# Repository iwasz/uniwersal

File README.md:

# uniwersal
Universal board and shields for it. Below is a photo of version 1.0

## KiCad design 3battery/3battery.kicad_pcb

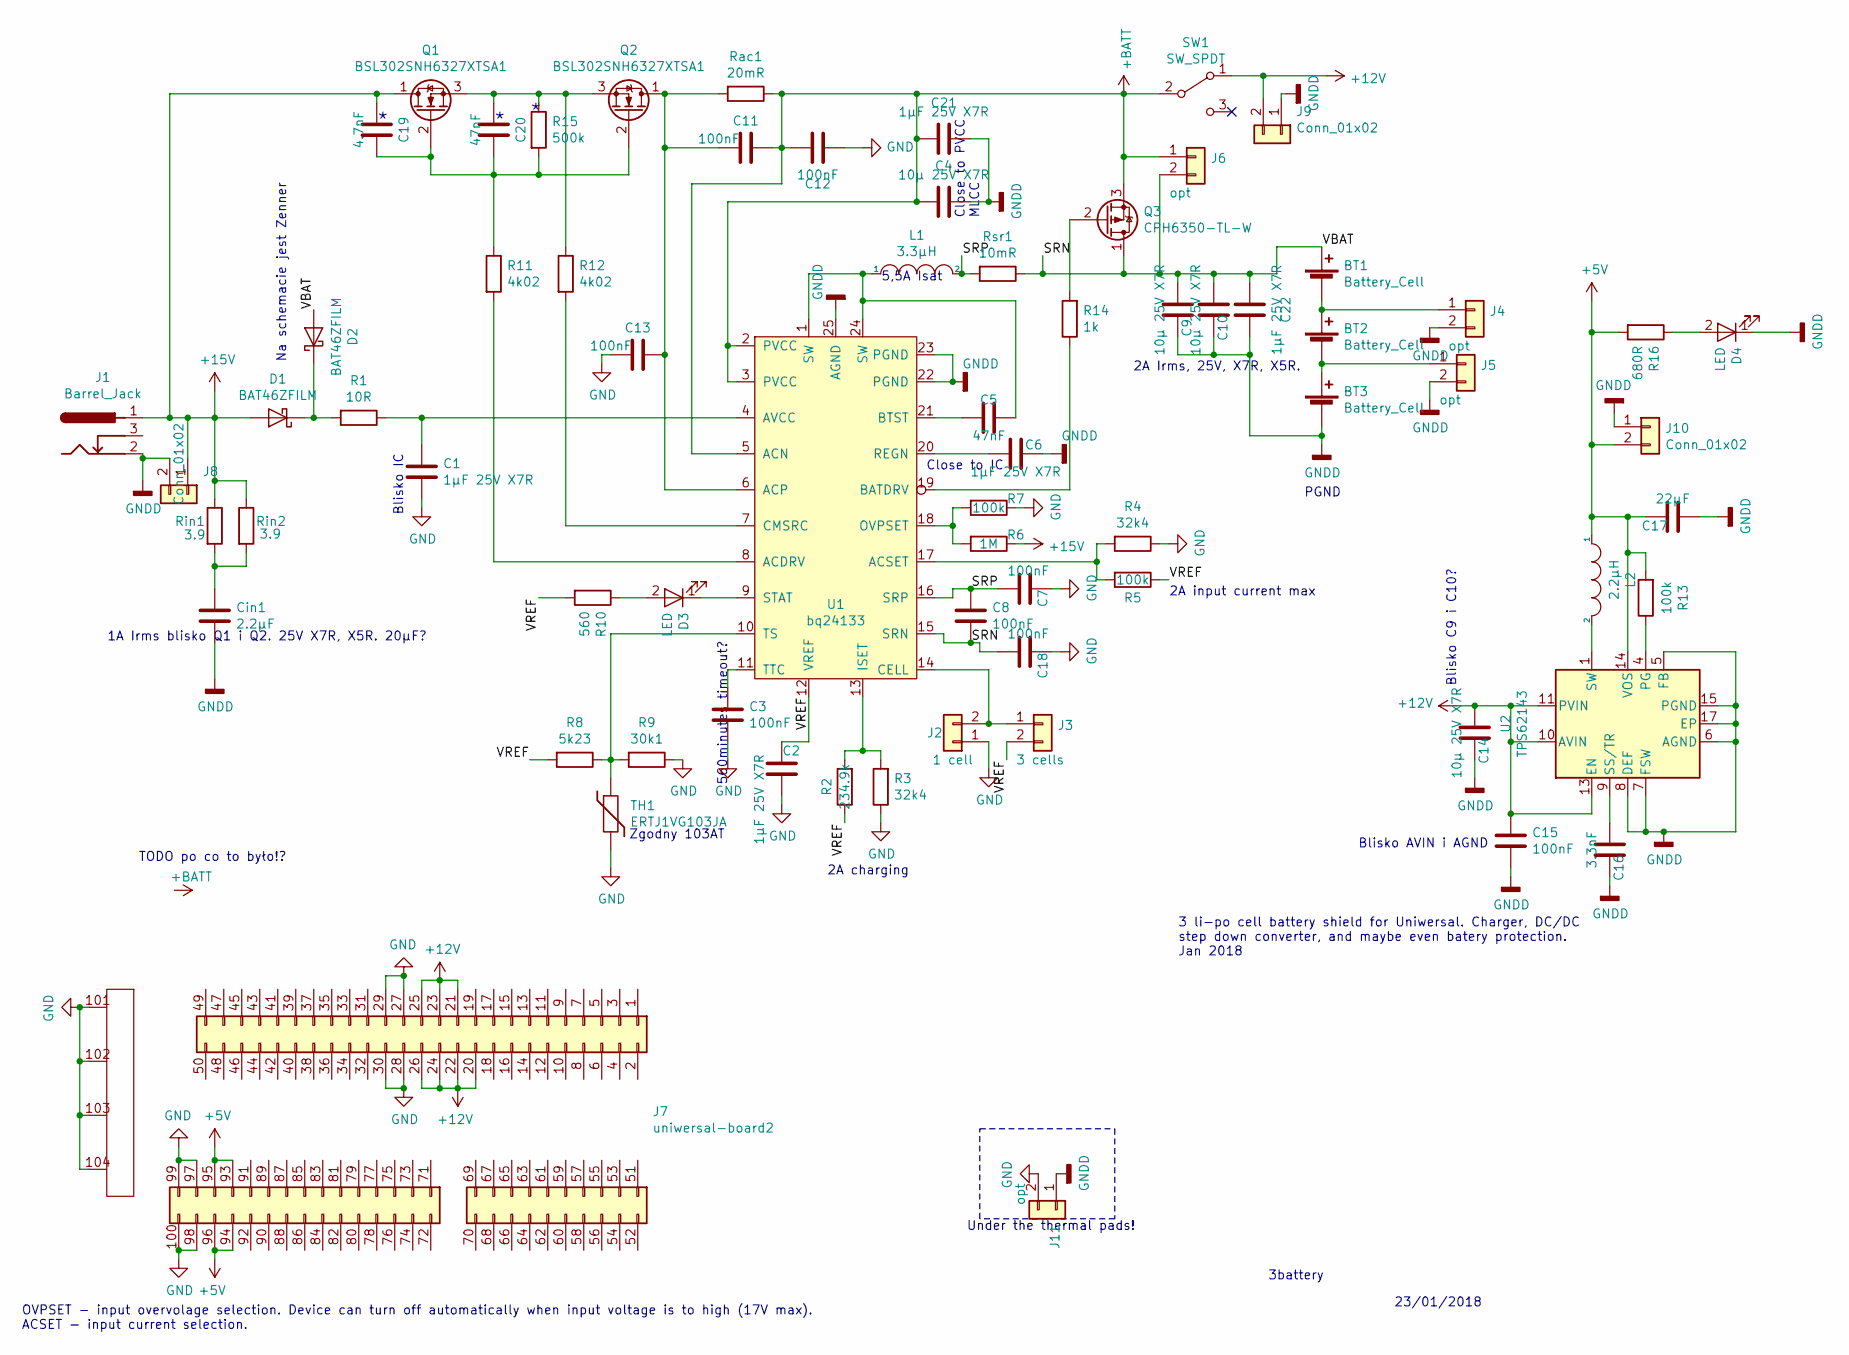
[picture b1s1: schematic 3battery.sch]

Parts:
BT1, BT2, BT3: Battery_Cell; BLM-BH18650-PC2
C1, C2, C6, C21, C22: 1µF 25V X7R; C_0805_2012Metric
C3, C7, C8, C11, C12, C13, C15, C18: 100nF; C_0603_1608Metric
C4, C9, C10, C14: 10µ 25V X7R; C_1206_3216Metric
C5, C20: 47nF; C_0603_1608Metric
C16: 3.3nF; C_0603_1608Metric
C17: 22µF; C_1206_3216Metric
C19: 4.7nF; C_0603_1608Metric
Cin1: 2.2µF; C_0805_2012Metric
D1, D2: BAT46ZFILM; D_SOD-123
D3, D4: LED; D_0805_2012Metric
J1: Barrel_Jack; BarrelJack_Horizontal
J2: 1 cell; SolderJumper-2_P1.3mm_Open_RoundedPad1.0x1.5mm
J3: 3 cells; SolderJumper-2_P1.3mm_Bridged_RoundedPad1.0x1.5mm
J4, J5, J6: opt; SolderJumper-2_P1.3mm_Open_RoundedPad1.0x1.5mm
J7: uniwersal-board2; uniwersal-board
J8, J9, J10: Conn_01x02; PinHeader_1x02_P2.54mm_Vertical
J11: opt; R_0402_1005Metric
L1: 3.3µH; L_7.3x7.3_H3.5
L2: 2.2µH; L_6.3x6.3_H3
Q1, Q2: BSL302SNH6327XTSA1; TSOP-6_1.65x3.05mm_P0.95mm-BSLMOSFET
Q3: CPH6350-TL-W; TSOT-23-6-POWER_MOSFET
R1: 10R; R_1206_3216Metric
R2: 234.9k; R_0603_1608Metric
R3, R4: 32k4; R_0603_1608Metric
R5, R7, R13: 100k; R_0603_1608Metric
R6: 1M; R_0603_1608Metric
R8: 5k23; R_0603_1608Metric
R9: 30k1; R_0603_1608Metric
R10: 560; R_0603_1608Metric
R11, R12: 4k02; R_0603_1608Metric
R14: 1k; R_0603_1608Metric
R15: 500k; R_0603_1608Metric
R16: 680R; R_0603_1608Metric
Rac1: 20mR; R_1206_3216Metric
Rin1, Rin2: 3.9; R_2010_5025Metric
Rsr1: 10mR; R_1206_3216Metric
SW1: SW_SPDT; SW_CuK_OS102011MA1QN1_SPDT_Angled
TH1: ERTJ1VG103JA; R_0603_1608Metric
U1: bq24133; R-PVQFN-N24
U2: TPS62143; QFN-16-1EP_3x3mm_P0.5mm_EP2.7x2.7mm_ThermalVias

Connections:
+5V: C17.1, J7.93 (Pin_23), J7.94 (Pin_24), J7.95 (Pin_25), J7.96 (Pin_26), J10.2, L2.1, R13.2, R16.2, U2.14 (VOS)
+12V: C14.2, C15.1, J7.20, J7.21, J7.22, J7.23, J7.24, J7.25, J7.26, J9.2, SW1.1 (A), U2.10 (AVIN), U2.11 (PVIN), U2.12 (PVIN), U2.13 (EN)
+15V: C19.1, D1.2 (A), J1.1, J8.1, Q1.1 (D), R6.1, Rin1.1, Rin2.1
+BATT: C4.2, C11.2, C12.1, C21.2, J6.1, Q3.3 (S), Rac1.1, SW1.2 (B), U1.2 (PVCC), U1.3 (PVCC), U1.5 (ACN)
/SRN: BT1.1 (+), C8.2, C9.2, C10.2, C18.2, C22.2, D2.2 (A), J6.2, Q3.1 (D), Rsr1.1, U1.15 (SRN)
/SRP: C7.2, C8.1, L1.2, Rsr1.2, U1.16 (SRP)
/VREF: C2.1, J3.2, R2.1, R5.1, R8.2, R10.2, U1.12 (VREF)
GND: C1.2, C2.2, C3.2, C7.1, C12.2, C13.1, C18.1, J2.1, J7.27, J7.28, J7.29, J7.30, J7.97 (Pin_27), J7.98 (Pin_28), J7.99 (Pin_29), J7.100 (Pin_30), J7.101, J7.102, J7.103, J7.104, J11.2, R3.1, R4.1, R7.1, R9.1, TH1.2
GNDD: BT3.2 (-), C4.1, C6.1, C9.1, C10.1, C14.1, C15.2, C16.1, C17.2, C21.1, C22.1, Cin1.2, D4.1 (K), J1.2, J4.2, J5.2, J8.2, J9.1, J10.1, J11.1, U1.22 (PGND), U1.23 (PGND), U1.25 (AGND), U2.5 (FB), U2.6 (AGND), U2.7 (FSW), U2.8 (DEF), U2.15 (PGND), U2.16 (PGND), U2.17 (EP)
unnamed: BT1.2 (-), BT2.1 (+), J4.1
unnamed: BT2.2 (-), BT3.1 (+), J5.1
unnamed: C1.1, R1.1, U1.4 (AVCC)
unnamed: C3.1, U1.11 (TTC)
unnamed: C5.1, L1.1, U1.1 (SW), U1.24 (SW)
unnamed: C5.2, U1.21 (BTST)
unnamed: C6.2, U1.20 (REGN)
unnamed: C11.1, C13.2, Q2.1 (D), Rac1.2, U1.6 (ACP)
unnamed: C16.2, U2.9 (SS/TR)
unnamed: C19.2, C20.2, Q1.2 (G), Q2.2 (G), R11.1, R15.2
unnamed: C20.1, Q1.3 (S), Q2.3 (S), R12.1, R15.1
unnamed: Cin1.1, Rin1.2, Rin2.2
unnamed: D1.1 (K), D2.1 (K), R1.2
unnamed: D3.1 (K), U1.9 (STAT)
unnamed: D3.2 (A), R10.1
unnamed: D4.2 (A), R16.1
unnamed: J2.2, J3.1, U1.14 (CELL)
unnamed: L2.2, U2.1 (SW), U2.2 (SW), U2.3 (SW)
unnamed: Q3.2 (G), R14.2
unnamed: R2.2, R3.2, U1.13 (ISET)
unnamed: R4.2, R5.2, U1.17 (ACSET)
unnamed: R6.2, R7.2, U1.18 (OVPSET)
unnamed: R8.1, R9.2, TH1.1, U1.10 (TS)
unnamed: R11.2, U1.8 (ACDRV)
unnamed: R12.2, U1.7 (CMSRC)
unnamed: R13.1, U2.4 (PG)
unnamed: R14.1, U1.19 (BATDRV)

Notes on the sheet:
Na schemacie jest Zenner
Blisko IC
3battery
23/01/2018
3 li-po cell battery shield for Uniwersal. Charger, DC/DC step down converter, and maybe even batery protection. Jan 2018
Blisko C9 i C10?
Blisko AVIN i AGND
OVPSET - input overvolage selection. Device can turn off automatically when input voltage is to high (17V max). ACSET - input current selection.
PGND
Close to PVCC MLCC
Close to IC
2A charging
2A input current max
560minutes timeout?
Zgodny 103AT
5,5A Isat
1A Irms blisko Q1 i Q2. 25V X7R, X5R. 20µF?
2A Irms, 25V, X7R, X5R.
Under the thermal pads!
TODO po co to było!?

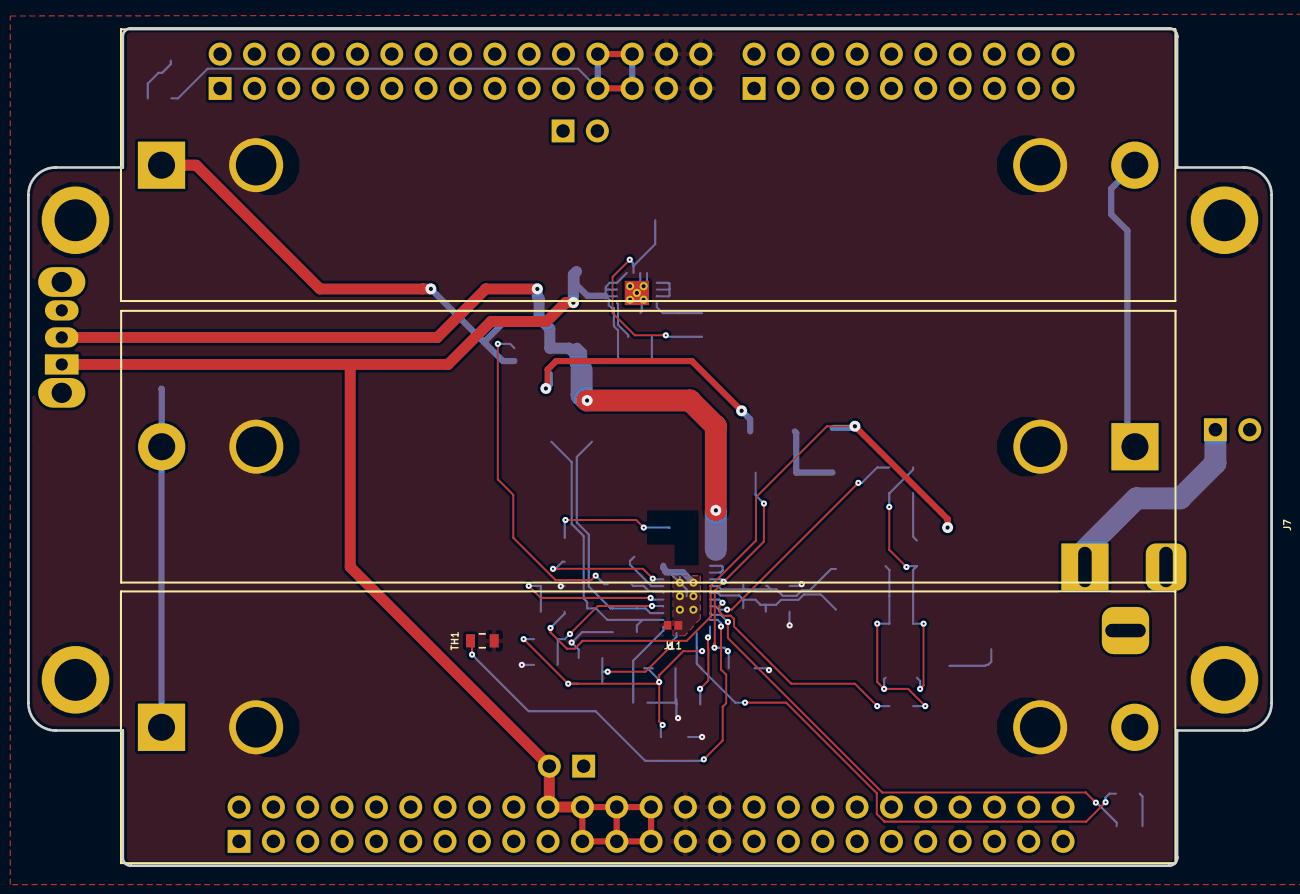
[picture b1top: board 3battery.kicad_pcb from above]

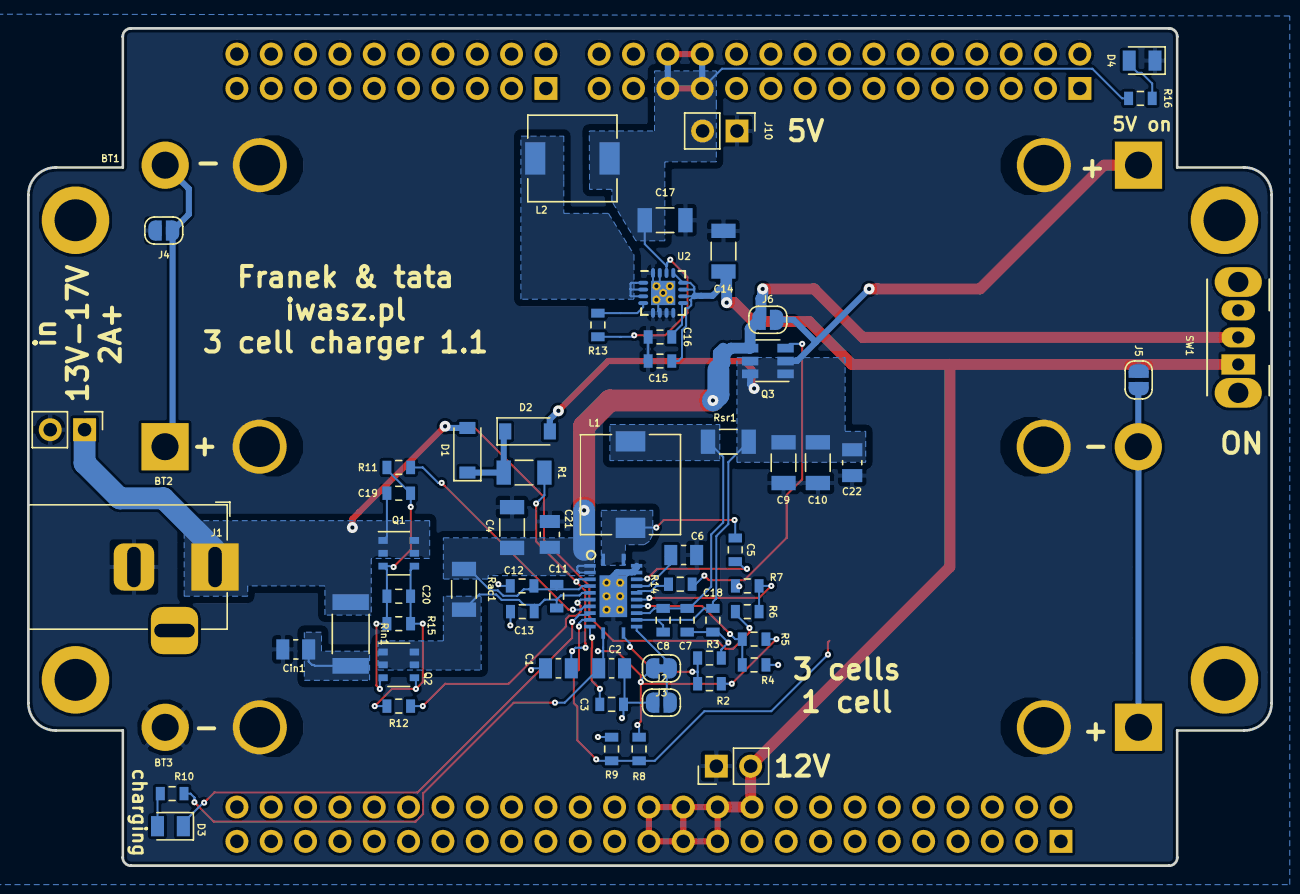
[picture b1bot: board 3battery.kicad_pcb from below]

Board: 2 copper layers, 92.0 x 61.9 mm, 69 parts (63 on the bottom side), 36 nets.

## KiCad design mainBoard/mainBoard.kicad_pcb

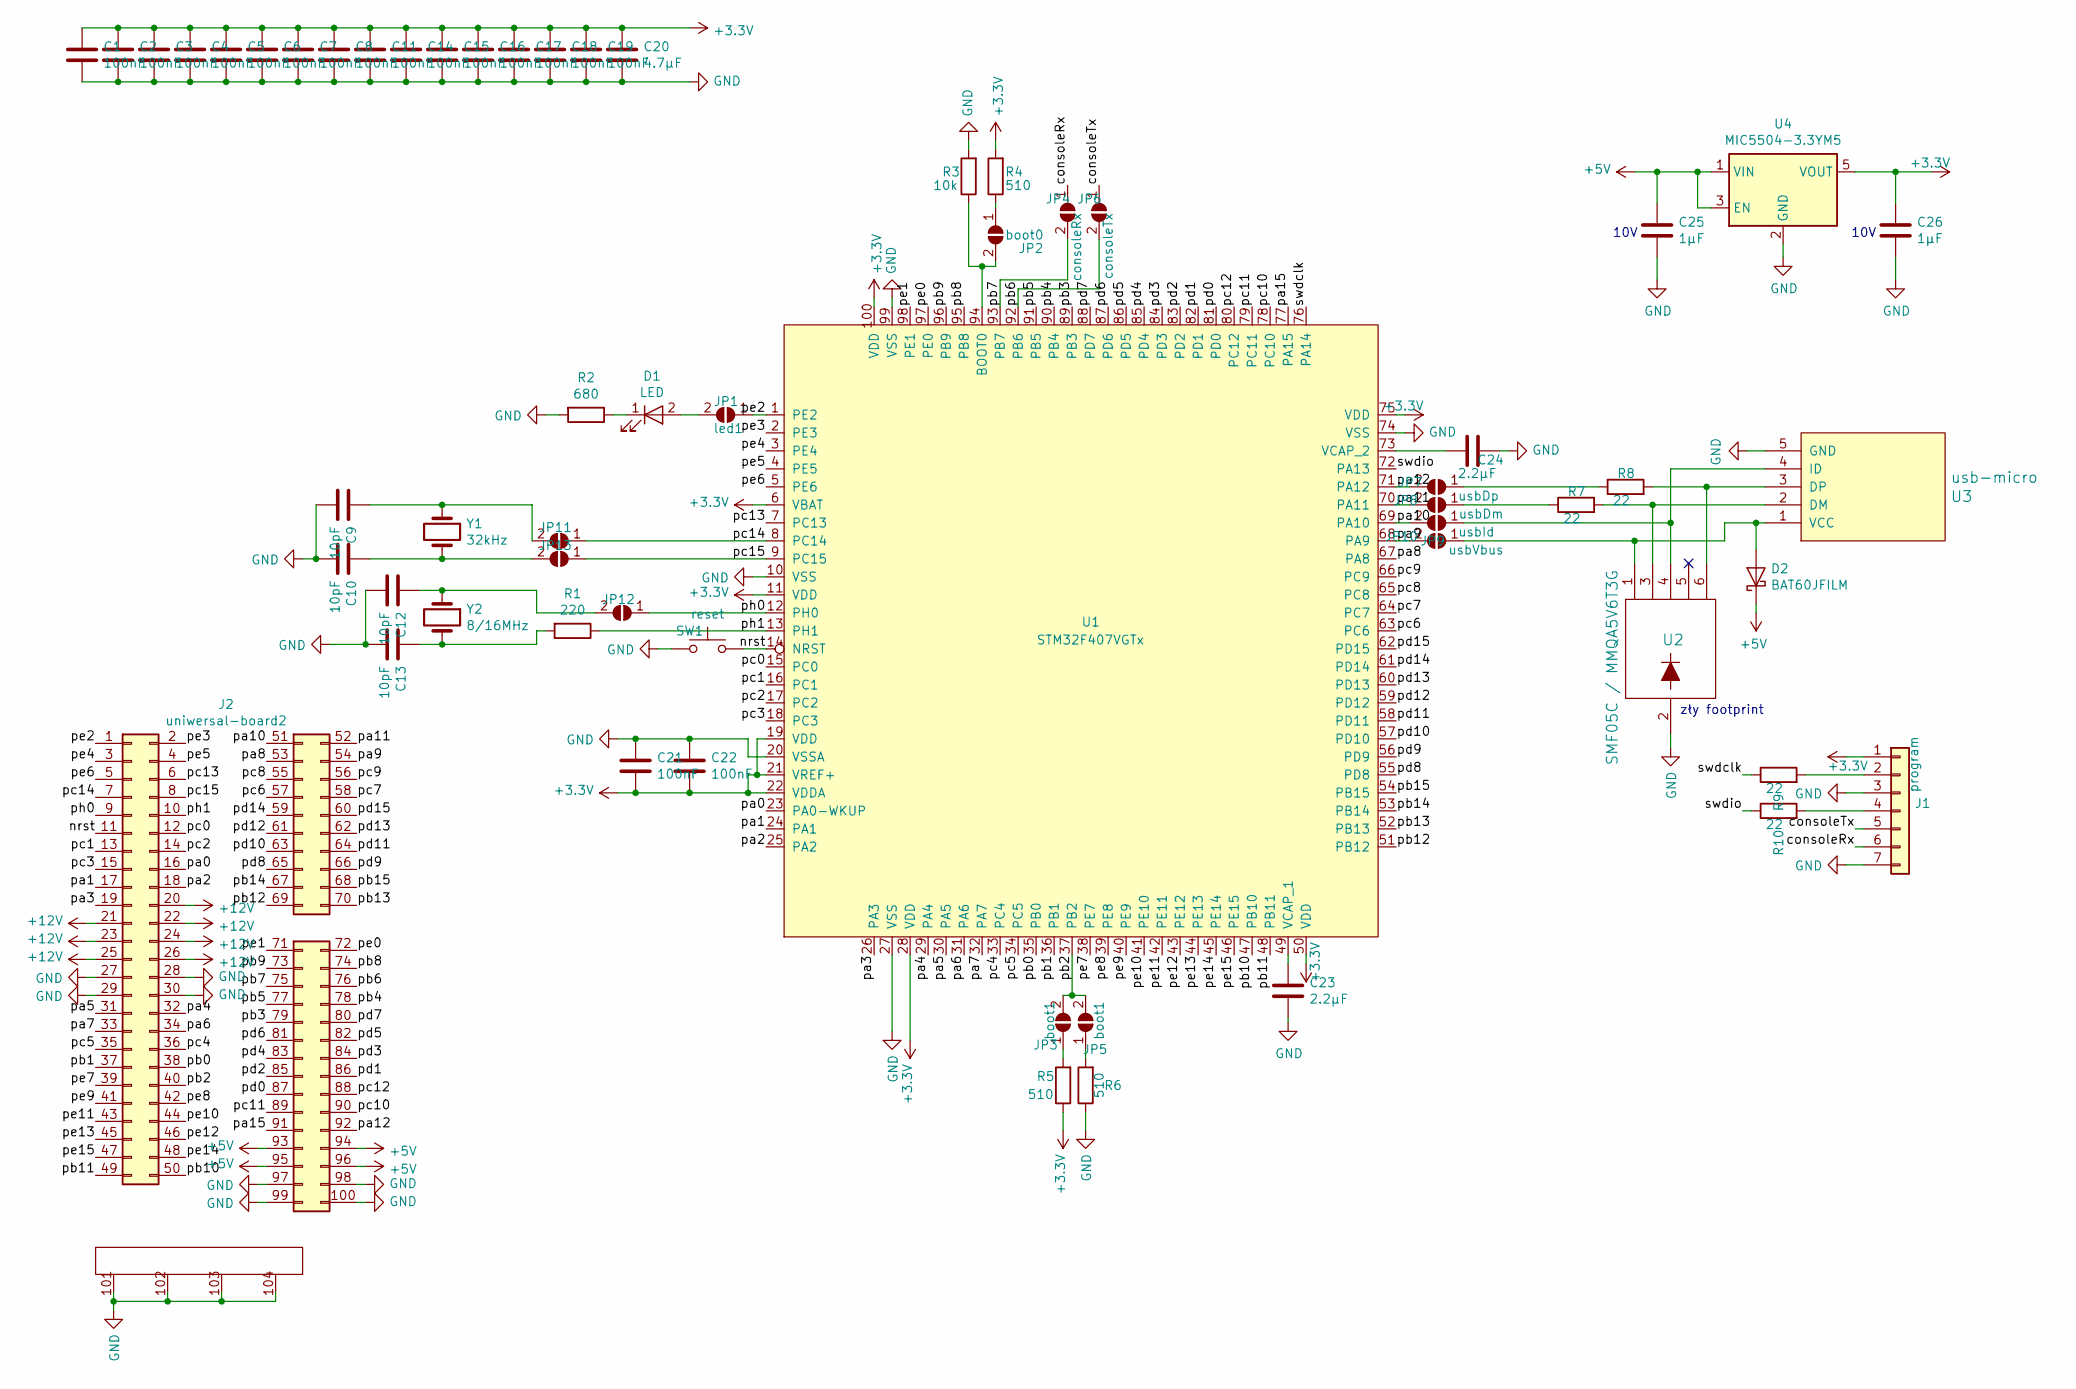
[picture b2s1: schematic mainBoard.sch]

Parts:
C1, C2, C3, C4, C5, C6, C7, C8, C11, C14, C15, C16, C17, C18, C19, C21, C22: 100nF; C_0603_1608Metric
C9, C10, C12, C13: 10pF; C_0603_1608Metric
C20: 4.7µF; C_1206_3216Metric
C23, C24: 2.2µF; C_1206_3216Metric
C25, C26: 1µF; C_0805_2012Metric
D1: LED; LED_0805_2012Metric
D2: BAT60JFILM; D_SOD-323
J1: program; PinHeader_1x07_P2.00mm_Vertical
J2: uniwersal-board2; uniwersal-board
JP1: led1; SolderJumper-2_P1.3mm_Open_RoundedPad1.0x1.5mm
JP2: boot0; SolderJumper-2_P1.3mm_Open_RoundedPad1.0x1.5mm
JP3, JP5: boot1; SolderJumper-2_P1.3mm_Open_RoundedPad1.0x1.5mm
JP4: consoleRx; SolderJumper-2_P1.3mm_Bridged_RoundedPad1.0x1.5mm
JP6: consoleTx; SolderJumper-2_P1.3mm_Bridged_RoundedPad1.0x1.5mm
JP7: usbDp; SolderJumper-2_P1.3mm_Bridged_RoundedPad1.0x1.5mm
JP8: usbDm; SolderJumper-2_P1.3mm_Bridged_RoundedPad1.0x1.5mm
JP9: usbId; SolderJumper-2_P1.3mm_Open_RoundedPad1.0x1.5mm
JP10: usbVbus; SolderJumper-2_P1.3mm_Open_RoundedPad1.0x1.5mm
JP11, JP13: x; SolderJumper-2_P1.3mm_Open_RoundedPad1.0x1.5mm
JP12: x32; SolderJumper-2_P1.3mm_Bridged_RoundedPad1.0x1.5mm
R1: 220; R_0603_1608Metric
R2: 680; R_0603_1608Metric
R3: 10k; R_0603_1608Metric
R4, R5, R6: 510; R_0603_1608Metric
R7, R8, R9, R10: 22; R_0603_1608Metric
SW1: reset; SW_Tactile_SPST_Angled_PTS645Vx83-2LFS
U1: STM32F407VGTx; LQFP-100_14x14mm_P0.5mm
U2: SMF05C / MMQA5V6T3G; SOT-363_SC-70-6
U3: usb-micro; conn_usb_B_micro_smd-2-nohole
U4: MIC5504-3.3YM5; SOT-23-5
Y1: 32kHz; Crystal_C38-LF_D3.0mm_L8.0mm_Horizontal
Y2: 8/16MHz; Crystal_HC49-4H_Vertical

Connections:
+3V3: C1.1, C2.1, C3.1, C4.1, C5.1, C6.1, C7.1, C8.1, C11.1, C14.1, C15.1, C16.1, C17.1, C18.1, C19.1, C20.1, C21.1, C22.2, C26.1, J1.1, R4.2, R5.1, U1.6 (VBAT), U1.11 (VDD), U1.19 (VDD), U1.21 (VREF+), U1.22 (VDDA), U1.28 (VDD), U1.50 (VDD), U1.75 (VDD), U1.100 (VDD), U4.5 (VOUT)
+5V: C25.1, D2.1 (K), J2.93 (Pin_23), J2.94 (Pin_24), J2.95 (Pin_25), J2.96 (Pin_26), U4.1 (VIN), U4.3 (EN)
+12V: J2.20, J2.21, J2.22, J2.23, J2.24, J2.25, J2.26
/consoleRx: J1.6, JP4.1 (A)
/consoleTx: J1.5, JP6.1 (A)
/nrst: J2.11, SW1.2, U1.14 (NRST)
/pa0: J2.16, U1.23 (PA0-WKUP)
/pa1: J2.17, U1.24 (PA1)
/pa2: J2.18, U1.25 (PA2)
/pa3: J2.19, U1.26 (PA3)
/pa4: J2.32, U1.29 (PA4)
/pa5: J2.31, U1.30 (PA5)
/pa6: J2.34, U1.31 (PA6)
/pa7: J2.33, U1.32 (PA7)
/pa8: J2.53 (Pin_3), U1.67 (PA8)
/pa9: J2.54, JP10.2 (B), U1.68 (PA9)
/pa10: J2.51 (Pin_1), JP9.2 (B), U1.69 (PA10)
/pa11: J2.52 (Pin_2), JP8.2 (B), U1.70 (PA11)
/pa12: J2.92 (Pin_22), JP7.2 (B), U1.71 (PA12)
/pa15: J2.91 (Pin_21), U1.77 (PA15)
/pb0: J2.38, U1.35 (PB0)
/pb1: J2.37, U1.36 (PB1)
/pb2: J2.40, JP3.2 (B), JP5.2 (B), U1.37 (PB2)
/pb3: J2.79 (Pin_9), U1.89 (PB3)
/pb4: J2.78 (Pin_8), U1.90 (PB4)
/pb5: J2.77 (Pin_7), U1.91 (PB5)
/pb6: J2.76 (Pin_6), JP6.2 (B), U1.92 (PB6)
/pb7: J2.75 (Pin_5), JP4.2 (B), U1.93 (PB7)
/pb8: J2.74 (Pin_4), U1.95 (PB8)
/pb9: J2.73 (Pin_3), U1.96 (PB9)
/pb10: J2.50, U1.47 (PB10)
/pb11: J2.49, U1.48 (PB11)
/pb12: J2.69, U1.51 (PB12)
/pb13: J2.70 (Pin_20), U1.52 (PB13)
/pb14: J2.67 (Pin_17), U1.53 (PB14)
/pb15: J2.68 (Pin_18), U1.54 (PB15)
/pc0: J2.12, U1.15 (PC0)
/pc1: J2.13, U1.16 (PC1)
/pc2: J2.14, U1.17 (PC2)
/pc3: J2.15, U1.18 (PC3)
/pc4: J2.36, U1.33 (PC4)
/pc5: J2.35, U1.34 (PC5)
/pc6: J2.57 (Pin_7), U1.63 (PC6)
/pc7: J2.58 (Pin_8), U1.64 (PC7)
/pc8: J2.55 (Pin_5), U1.65 (PC8)
/pc9: J2.56 (Pin_6), U1.66 (PC9)
/pc10: J2.90 (Pin_20), U1.78 (PC10)
/pc11: J2.89 (Pin_19), U1.79 (PC11)
/pc12: J2.88 (Pin_18), U1.80 (PC12)
/pc13: J2.6, U1.7 (PC13)
/pc14: J2.7, JP11.1 (A), U1.8 (PC14)
/pc15: J2.8, JP13.1 (A), U1.9 (PC15)
/pd0: J2.87 (Pin_17), U1.81 (PD0)
/pd1: J2.86 (Pin_16), U1.82 (PD1)
/pd2: J2.85 (Pin_15), U1.83 (PD2)
/pd3: J2.84 (Pin_14), U1.84 (PD3)
/pd4: J2.83 (Pin_13), U1.85 (PD4)
/pd5: J2.82 (Pin_12), U1.86 (PD5)
/pd6: J2.81, U1.87 (PD6)
/pd7: J2.80 (Pin_10), U1.88 (PD7)
/pd8: J2.65 (Pin_15), U1.55 (PD8)
/pd9: J2.66 (Pin_16), U1.56 (PD9)
/pd10: J2.63 (Pin_13), U1.57 (PD10)
/pd11: J2.64 (Pin_14), U1.58 (PD11)
/pd12: J2.61 (Pin_11), U1.59 (PD12)
/pd13: J2.62, U1.60 (PD13)
/pd14: J2.59 (Pin_9), U1.61 (PD14)
/pd15: J2.60 (Pin_10), U1.62 (PD15)
/pe0: J2.72 (Pin_2), U1.97 (PE0)
/pe1: J2.71 (Pin_1), U1.98 (PE1)
/pe2: J2.1, JP1.1 (A), U1.1 (PE2)
/pe3: J2.2, U1.2 (PE3)
/pe4: J2.3, U1.3 (PE4)
/pe5: J2.4, U1.4 (PE5)
/pe6: J2.5, U1.5 (PE6)
/pe7: J2.39, U1.38 (PE7)
/pe8: J2.42, U1.39 (PE8)
/pe9: J2.41, U1.40 (PE9)
/pe10: J2.44, U1.41 (PE10)
/pe11: J2.43, U1.42 (PE11)
/pe12: J2.46, U1.43 (PE12)
/pe13: J2.45, U1.44 (PE13)
/pe14: J2.48, U1.45 (PE14)
/pe15: J2.47, U1.46 (PE15)
/ph0: J2.9, JP12.1 (A), U1.12 (PH0)
/ph1: J2.10, R1.1, U1.13 (PH1)
/swdclk: R9.1, U1.76 (PA14)
/swdio: R10.1, U1.72 (PA13)
GND: C1.2, C2.2, C3.2, C4.2, C5.2, C6.2, C7.2, C8.2, C9.1, C10.1, C11.2, C12.1, C13.1, C14.2, C15.2, C16.2, C17.2, C18.2, C19.2, C20.2, C21.2, C22.1, C23.2, C24.1, C25.2, C26.2, J1.3, J1.7, J2.27, J2.28, J2.29, J2.30, J2.97 (Pin_27), J2.98 (Pin_28), J2.99 (Pin_29), J2.100 (Pin_30), J2.101, J2.102, J2.103, J2.104, R2.2, R3.2, R6.1, SW1.1, U1.10 (VSS), U1.20 (VSSA), U1.27 (VSS), U1.74 (VSS), U1.99 (VSS), U2.2, U3.5 (GND), U4.2 (GND)
unnamed: C9.2, JP11.2 (B), Y1.1
unnamed: C10.2, JP13.2 (B), Y1.2
unnamed: C12.2, JP12.2 (B), Y2.1
unnamed: C13.2, R1.2, Y2.2
unnamed: C23.1, U1.49 (VCAP_1)
unnamed: C24.2, U1.73 (VCAP_2)
unnamed: D1.1 (K), R2.1
unnamed: D1.2 (A), JP1.2 (B)
unnamed: D2.2 (A), JP10.1 (A), U2.1, U3.1 (VCC)
unnamed: J1.2, R9.2
unnamed: J1.4, R10.2
unnamed: JP2.1 (A), R4.1
unnamed: JP2.2 (B), R3.1, U1.94 (BOOT0)
unnamed: JP3.1 (A), R5.2
unnamed: JP5.1 (A), R6.2
unnamed: JP7.1 (A), R8.1
unnamed: JP8.1 (A), R7.1
unnamed: JP9.1 (A), U2.4, U3.4 (ID)
unnamed: R7.2, U2.3, U3.2 (DM)
unnamed: R8.2, U2.6, U3.3 (DP)

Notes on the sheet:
10V
zły footprint

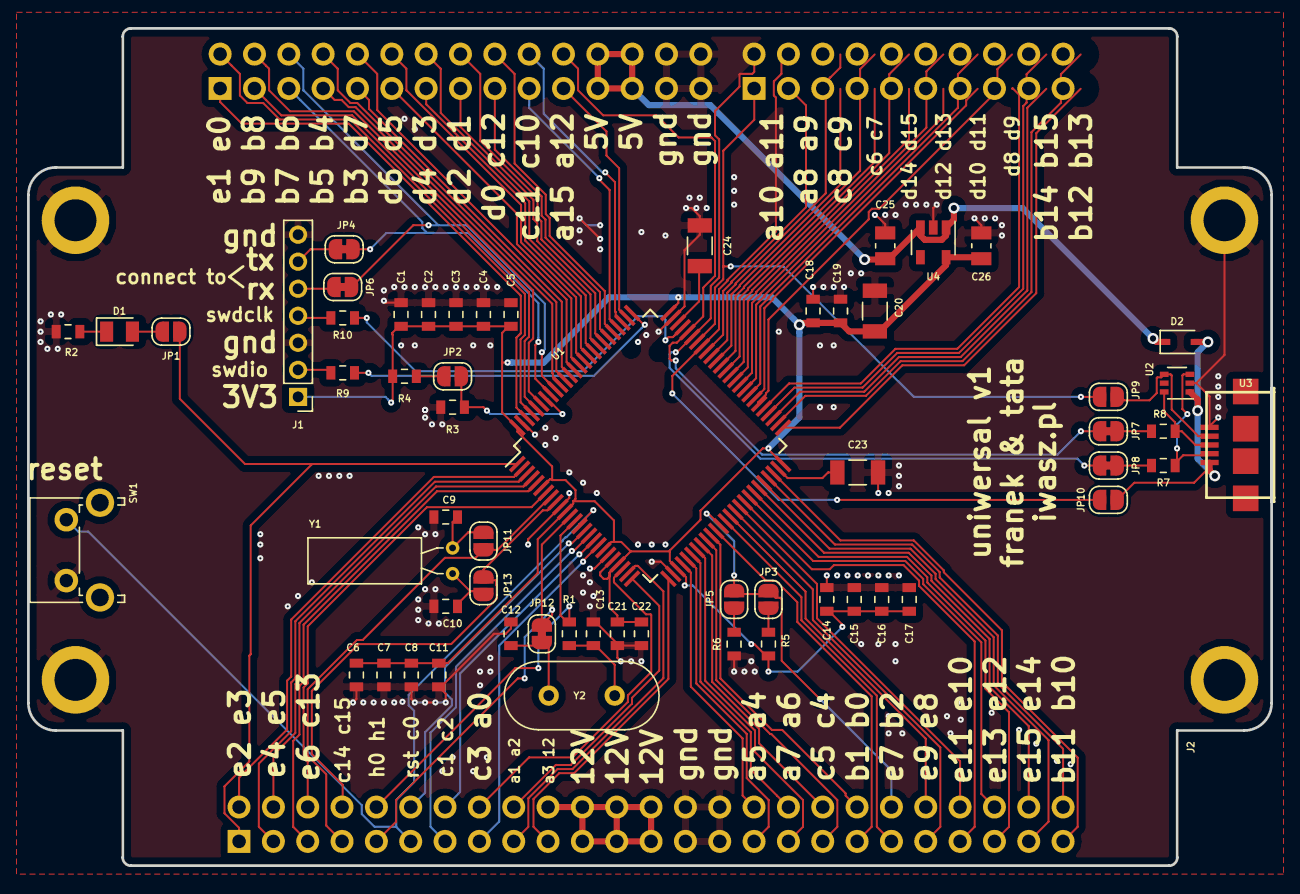
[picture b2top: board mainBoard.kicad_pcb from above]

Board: 2 copper layers, 92.0 x 61.9 mm, 60 parts (0 on the bottom side), 109 nets.

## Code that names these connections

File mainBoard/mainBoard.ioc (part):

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Mcu.Name=STM32F407V(E-G)Tx
Mcu.Package=LQFP100
Mcu.UserName=STM32F407VGTx
PA10.Mode=OTG/Dual_Role_Device
PA10.Signal=USB_OTG_FS_ID
PA11.Mode=OTG/Dual_Role_Device
PA11.Signal=USB_OTG_FS_DM
PA12.Mode=OTG/Dual_Role_Device
PA12.Signal=USB_OTG_FS_DP
PA9.Signal=GPIO_Input
PB6.Mode=Asynchronous
PB6.Signal=USART1_TX
PB7.Mode=Asynchronous
PB7.Signal=USART1_RX
PE2.Signal=GPIO_Output
RCC.HSE_VALUE=25000000
RCC.SYSCLKFreq_VALUE=16000000

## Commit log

2018-01-30 Initial
2018-02-04 Main board and proto-board added
2018-02-05 4 layers, but I plan to make it only 2.
2018-02-07 Gerbers directory added, and domcumentation improved
2018-04-09 Bug-fixes. 3 battery soldered and working.
